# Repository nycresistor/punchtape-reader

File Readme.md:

Hardware
--------

punchtape.dxf has the basic mechanical design of the read head. The head is bolted together with M3 hardware.

boards/5mm-phototransistors contains Eagle CAD files for the LED emitter and phototransistor boards.

Software
--------

The reader is implemented as an Arduino sketch in punchtape-reader/punchtape-reader.ino. I'm using a Teensy++ 2.0
at present but it should work with any ordinary Arduino variant. You'll have to alter the pin assignments at the top
of the file, though.

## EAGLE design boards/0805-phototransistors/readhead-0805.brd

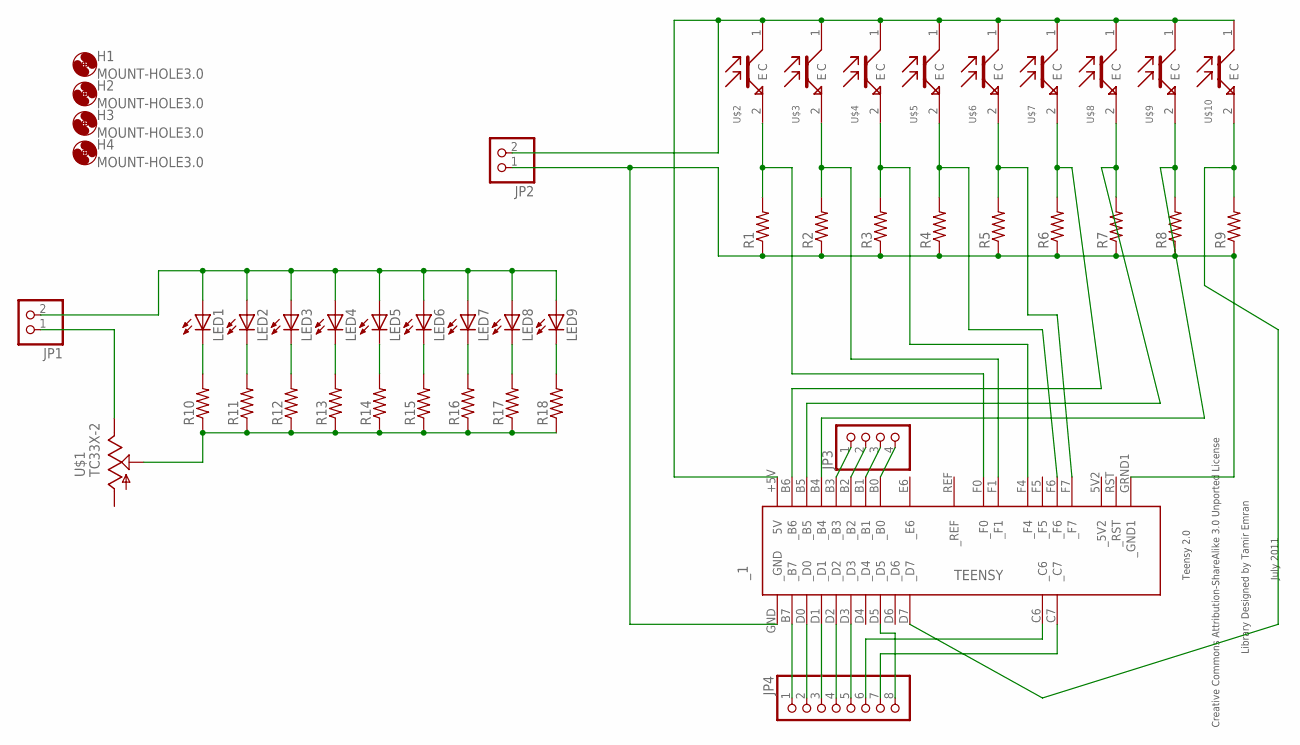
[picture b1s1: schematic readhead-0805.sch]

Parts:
H1, H2, H3, H4: MOUNT-HOLE3.0; 3,0
JP1, JP2: PINHD-1X2; 1X02
JP3: PINHD-1X4; 1X04
JP4: PINHD-1X8; 1X08
LED1, LED2, LED3, LED4, LED5, LED6, LED7, LED8, LED9: LEDCHIPLED_0805; CHIPLED_0805
R1, R2, R3, R4, R5, R6, R7, R8, R9, R10, R11, R12, R13, R14, R15, R16, R17, R18: R-US_R0805; R0805
U$1: TC33X-2
U$2, U$3, U$4, U$5, U$6, U$7, U$8, U$9, U$10: OP501DA; R0805
_1: TEENSY

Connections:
unnamed: LED1.C, R10.2
unnamed: LED2.C, R11.2
unnamed: LED3.C, R12.2
unnamed: LED4.C, R13.2
unnamed: LED5.C, R14.2
unnamed: LED6.C, R15.2
unnamed: LED7.C, R16.2
unnamed: LED8.C, R17.2
unnamed: LED9.C, R18.2
unnamed: R3.2, U$4.2 (E), _1.F4 (_F4)
unnamed: R2.2, U$3.2 (E), _1.F1 (_F1)
unnamed: R4.2, U$5.2 (E), _1.F6 (_F6)
unnamed: R5.2, U$6.2 (E), _1.F7 (_F7)
unnamed: R6.2, U$7.2 (E), _1.B6 (_B6)
unnamed: JP3.1, _1.B3 (_B3)
unnamed: JP2.1, R1.1, R2.1, R3.1, R4.1, R5.1, R6.1, R7.1, R8.1, R9.1, _1.GND (_GND), _1.GRND1 (_GND1)
unnamed: R1.2, U$2.2 (E), _1.F0 (_F0)
unnamed: JP1.2, LED1.A, LED2.A, LED3.A, LED4.A, LED5.A, LED6.A, LED7.A, LED8.A, LED9.A
unnamed: R10.1, R11.1, R12.1, R13.1, R14.1, R15.1, R16.1, R17.1, R18.1, U$1.P$2 (S)
unnamed: JP1.1, U$1.P$3 (E)
unnamed: JP2.2, U$2.1 (C), U$3.1 (C), U$4.1 (C), U$5.1 (C), U$6.1 (C), U$7.1 (C), U$8.1 (C), U$9.1 (C), U$10.1 (C), _1.+5V (5V)
unnamed: JP3.2, _1.B2 (_B2)
unnamed: JP3.3, _1.B1 (_B1)
unnamed: JP3.4, _1.B0 (_B0)
unnamed: JP4.1, _1.B7 (_B7)
unnamed: JP4.2, _1.D0 (_D0)
unnamed: JP4.3, _1.D1 (_D1)
unnamed: JP4.4, _1.D2 (_D2)
unnamed: JP4.5, _1.D3 (_D3)
unnamed: JP4.6, _1.C6 (_C6)
unnamed: JP4.7, _1.C7 (_C7)
unnamed: JP4.8, _1.D5 (_D5)
unnamed: R7.2, U$8.2 (E), _1.B5 (_B5)
unnamed: R8.2, U$9.2 (E), _1.B4 (_B4)
unnamed: R9.2, U$10.2 (E), _1.D7 (_D7)

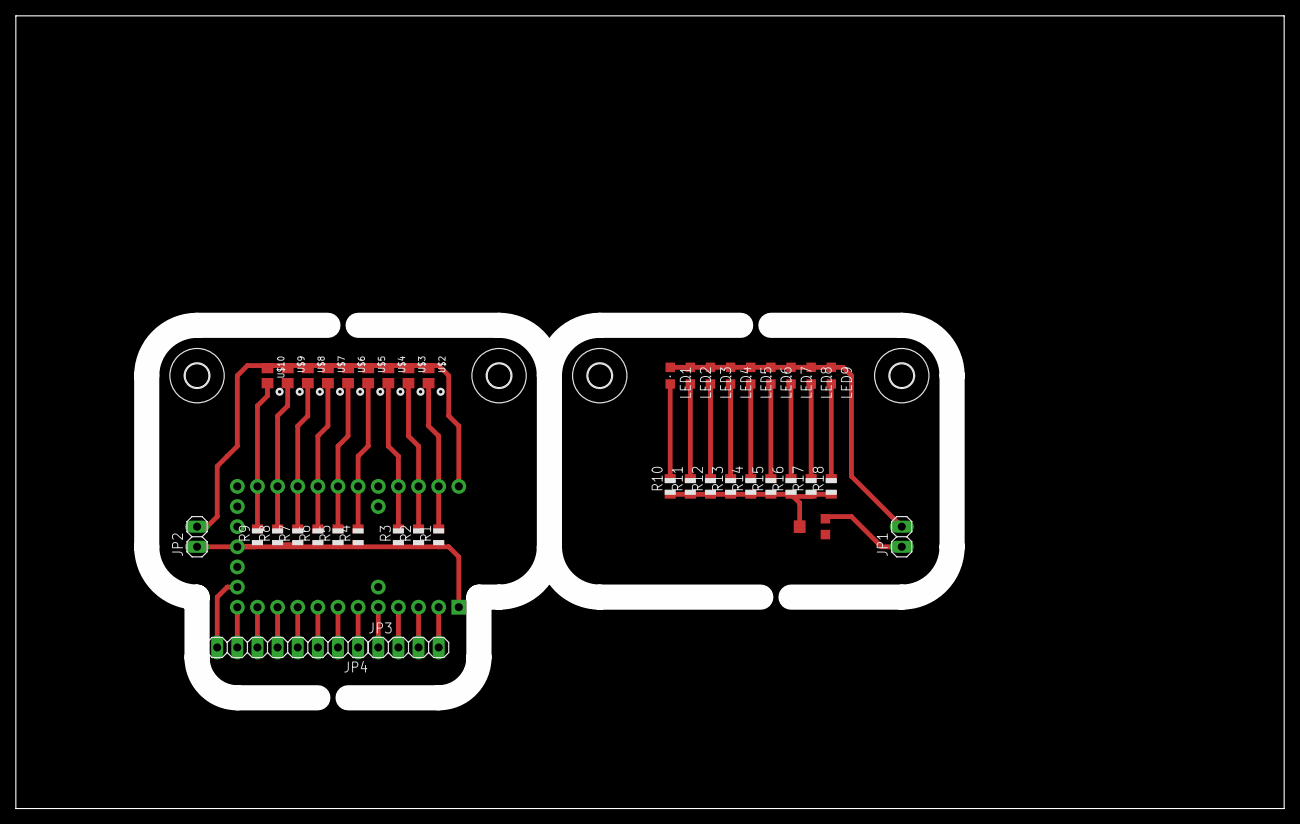
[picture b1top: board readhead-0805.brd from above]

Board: 2 copper layers, 156.8 x 96.8 mm, 46 parts (1 on the bottom side), 35 nets.

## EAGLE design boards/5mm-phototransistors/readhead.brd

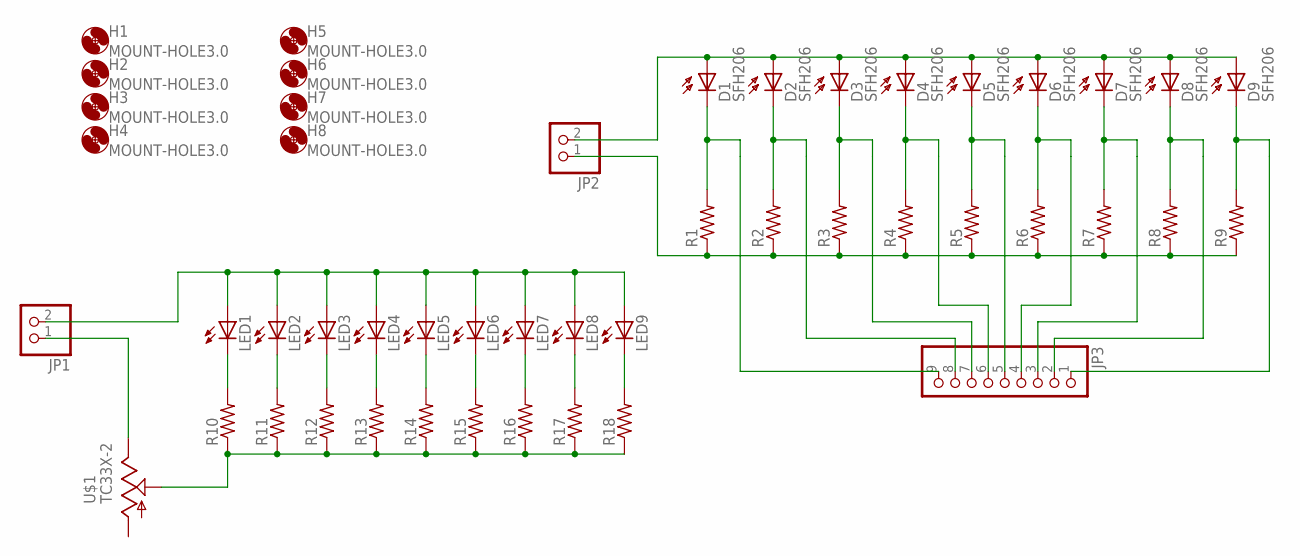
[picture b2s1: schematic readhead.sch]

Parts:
D1, D2, D3, D4, D5, D6, D7, D8, D9: SFH206
H1, H2, H3, H4, H5, H6, H7, H8: MOUNT-HOLE3.0; 3,0
JP1, JP2: PINHD-1X2; 1X02
JP3: PINHD-1X9; 1X09
LED1, LED2, LED3, LED4, LED5, LED6, LED7, LED8, LED9: LED5MM
R1, R2, R3, R4, R5, R6, R7, R8, R9, R10, R11, R12, R13, R14, R15, R16, R17, R18: R-US_R0805; R0805
U$1: TC33X-2

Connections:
unnamed: LED1.K (C), R10.2
unnamed: LED2.K (C), R11.2
unnamed: LED3.K (C), R12.2
unnamed: LED4.K (C), R13.2
unnamed: LED5.K (C), R14.2
unnamed: LED6.K (C), R15.2
unnamed: LED7.K (C), R16.2
unnamed: LED8.K (C), R17.2
unnamed: LED9.K (C), R18.2
unnamed: D1.K (C), JP3.9, R1.2
unnamed: D2.K (C), JP3.8, R2.2
unnamed: D3.K (C), JP3.7, R3.2
unnamed: D4.K (C), JP3.6, R4.2
unnamed: D5.K (C), JP3.5, R5.2
unnamed: D6.K (C), JP3.4, R6.2
unnamed: D7.K (C), JP3.3, R7.2
unnamed: D8.K (C), JP3.2, R8.2
unnamed: D9.K (C), JP3.1, R9.2
unnamed: JP2.1, R1.1, R2.1, R3.1, R4.1, R5.1, R6.1, R7.1, R8.1, R9.1
unnamed: D1.A, D2.A, D3.A, D4.A, D5.A, D6.A, D7.A, D8.A, D9.A, JP2.2
unnamed: JP1.2, LED1.A, LED2.A, LED3.A, LED4.A, LED5.A, LED6.A, LED7.A, LED8.A, LED9.A
unnamed: R10.1, R11.1, R12.1, R13.1, R14.1, R15.1, R16.1, R17.1, R18.1, U$1.P$2 (S)
unnamed: JP1.1, U$1.P$3 (E)

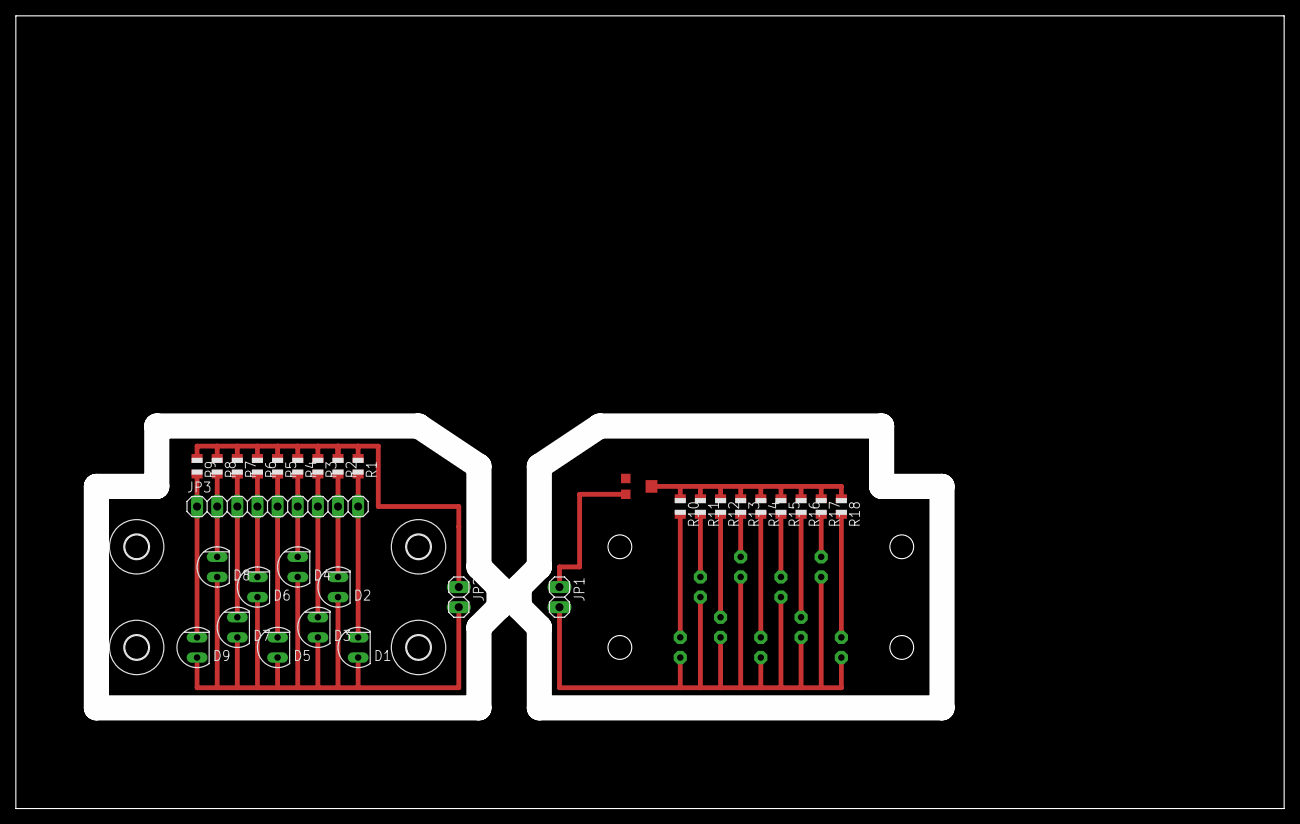
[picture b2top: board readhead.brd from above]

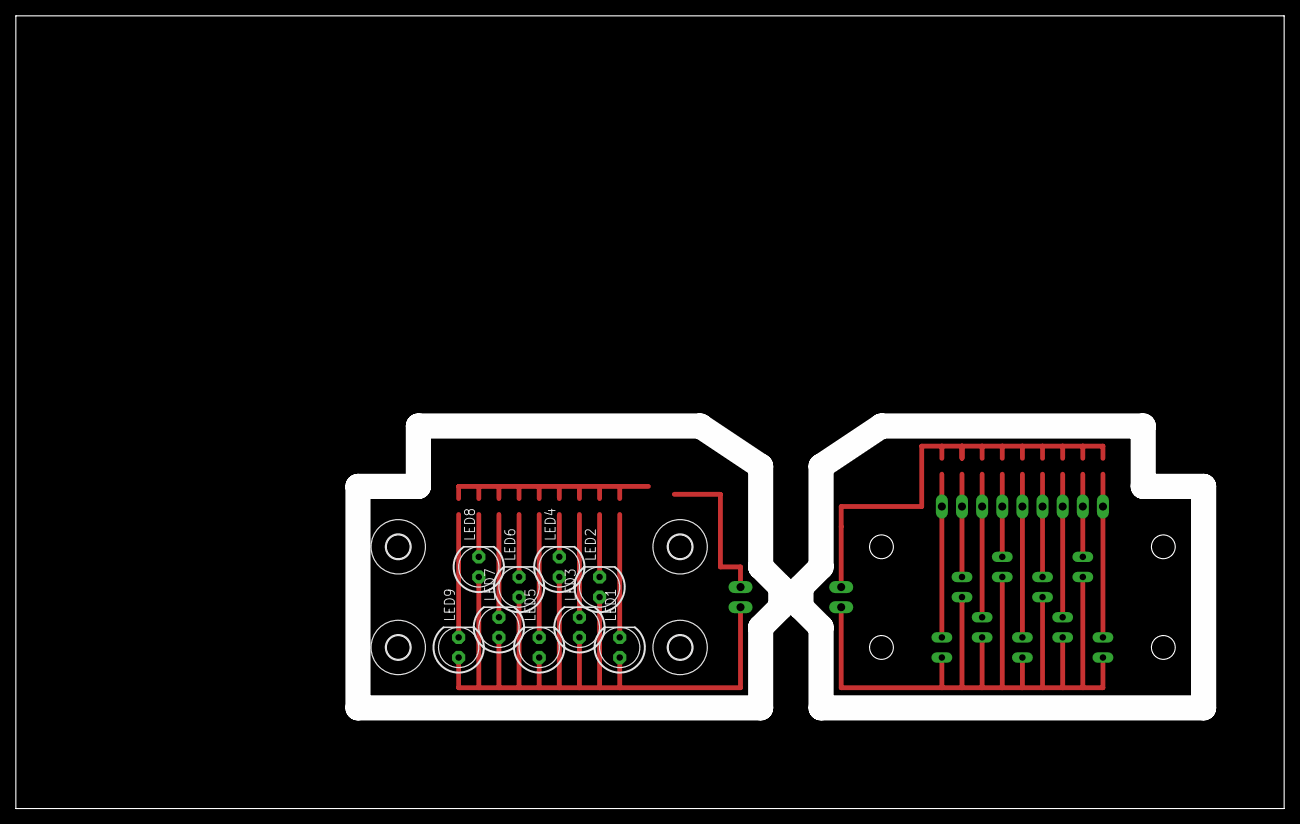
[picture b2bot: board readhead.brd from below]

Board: 2 copper layers, 156.8 x 96.8 mm, 48 parts (13 on the bottom side), 23 nets.

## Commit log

2013-05-09 adding readme
2013-05-09 some futzing around to increase response time don't use pin 6; there's already an LED on it on the teensy 2++
2013-05-09 add detailed instructions for building circuit
2013-05-10 current version; works with pathetic led-led version of the reader.
2013-05-10 5mm leds (the phototransistors we have...), new pattern
2013-05-10 made boards for new hardware; finished mechanical design for read head
2013-05-11 finalized version for new hardware
2013-05-11 adding tapes
2013-05-12 filtering noise
2013-05-16 v3 of reader started
2013-05-16 new read head board
2016-05-15 adding 2 clause bsd license

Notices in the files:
parts and their libraries:
teensy: Licensed Under Creative Commons
teensy: Creative Commons Attribution-ShareAlike 3.0 Unported License
teensy: Licensed Under Creative Commons Attribution-ShareAlike 3.0 Unported (CC BY-SA 3.0)
